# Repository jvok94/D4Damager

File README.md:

# D4 Damager
The D4 Damager is a fully-featured broadcast audio processor for AM or FM broadcasting. It can also be used as a ham radio voice processor. The D4 Damager combines six main 
features:

* **Fast peak limiting:** Prevents loud sounds from overmodulating your transmitter.
* **Compression:** A high (variable) gain input stage allows you to optionally overdrive the limiter, turning it into a compressor. This increases your audio volume without 
overmodulating, allowing you to better overcome background noise and compete with other stations.
* **Peak clipping:** Catches brief transients that overshoot the limiter, to prevent even very brief overmodulation. The limiter ensures that any clipping will only be brief and 
so does not much affect the sound.
* **Pre-emphasis:** Required for all FM transmitters, a modified version of pre-emphasis can also be used with AM transmitters to improve clarity.
* **Variable de-emphasis:** Automatically rolls off some or all of the pre-emphasis as necessary to prevent overmodulation due to the high-frequency boost.
* **Low-pass filter**: Rolls off any high frequency content that exceeds the transmitter's allowed bandwidth.

Full technical documentation will be added as soon as I get round to it.

## D4 Damager Main Board

This board implements a complete mono audio processor. For mono operation, two input connectors (J5 and J6) are provided to sum stereo sources to mono. Two boards can be linked 
together for stereo operation by joining the "STEREO LINK" connector (J4) on each board.

The PCB includes a full power supply requiring only a 15-0-15VAC (30VAC center tapped) supply from an external transformer. The power supply on a single PCB is capable of 
powering a full stereo system including all accessories (simply leave the power supply components un-populated on the second PCB). +/-15VDC power is also available on the two 
"EXT PWR" connectors (J8 and J9). Alternatively these connectors can be used to power the D4 Damager from an external +/-15VDC regulated PSU, in which case there is no need to 
fit the power supply components on the main PCB.

Controls are provided for:

* **Input gain (RV6):** Used both to match the D4 Damager to the signal level from the external audio source, and also to control how hard the limiter is driven to achieve the 
desired amount of compression.
* **Release time (RV3):** Controls how quickly the compressor/limiter returns to full gain after a transient. Influences how aggressive the compressor will sound.
* **Ratio (RV1):** Sets the maximum gain of the compressor/limiter during quiet passages. Useful to prevent excessive gain from boosting background noise, hum, hiss, etc.
* **Clipper clearance (RV4):** Sets the difference (clearance) between the limiter's output level and the clipper's clipping level. Used to trade off between maximum volume and 
minimum distortion.
* **Output gain (RV5):** Used to match the output level to your transmitter. Has no affect on the sound.

In a mono system, you have the choice of using either PCB-mount potentiometers (Bourns PTD90 series), or external panel-mount potentiometers wired to the board. In a stereo 
system, you will need to use panel-mount dual gang potentiometers to control both channels at once. In this case the two series connected dual-gang 500k potentiometers (RV1 and 
RV3) can be replaced with single 1M units. Take care to use the correct potentiometer law (RV4-RV6 are antilog types, which are unusual).

## LED Meter Bridge

Optional accessory containing four separate six-segment LED meters showing:

* Input signal level/limiter drive (VU response ref. to +12VU)
* Limiter gain reduction (reads right-to-left as standard for compressors)
* Pre-emphasis reduction (reads right-to-left)
* Output signal level (VU response ref. to +6VU)

Single connection to the main PCB via "METER BRIDGE" connector (J3) carries all signals and power. Use two PCBs in a stereo system.

## Balanced IO Card

Converts unbalanced inputs and outputs from/to balanced signals for connection to professional studio equipment. Contains two balanced receivers for stereo input, and two 
balanced transmitters for stereo output. Additionally contains two MONITOR outputs which are fully de-emphasised to drive studio monitors. All balanced inputs and outputs are 
available on both XLR and 1/4" TRS connectors.

Powered from main PCB via "EXT PWR" connector (J8 or J9).

## BoM Versions

Several different BoM versions are available to account for different broadcast standards around the world:

* **BoM fm na.xlsx:** For FM broadcasters in ITU Region 2 (North/South America). 15kHz audio bandwidth, 75us pre-emphasis time constant.
* **BoM fm row.xlsx:** For FM broadcasters in ITU Regions 1 (Africa, Europe, Middle East, North Asia) and 3 (South Asia, Oceania). 15kHz audio bandwidth, 50us pre-emphasis time 
constant.
* **BoM am na.xlsx:** For AM broadcasters in ITU Region 2 (North/South America). 5kHz audio bandwdith, pre-emphasis according to NRSC-1-C curve.
* **BoM am row.xlsx:** For AM broadcasters in ITU Regions 1 (Africa, Europe, Middle East, North Asia) and 3 (South Asia, Oceania). 4.5kHz audio bandwidth, pre-emphasis 
according to modified version of NRSC-1-C curve for reduced bandwidth.

BoM variants apply to main PCB and balanced IO card. LED VU meter card is the same worldwide.

## Initial calibration

You will need:

* Multimeter or DC voltmeter
* Dual-channel oscilloscope or audio millivolt meter
* Sine wave audio signal generator (you can use an app on your phone/PC for this, e.g. https://play.google.com/store/apps/details?id=com.keuwl.functiongenerator)

### Main PCB

Calibration should be done with no signal applied.

1. Adjust RV2 (SET DC) for 0.0mV DC offset on U1 pin 7.
2. Adjust RV7 (SET DC) for 0.0mV DC offset on U6 pin 1.

### LED VU Meter

Calibration should be done with LED VU meter PCB connected to main PCB. Make sure controls on main PCB are set as follows:

* RV1, RV3 fully clockwise.
* RV4, RV5, RV6 fully counter-clockwise.

1. Adjust RV1 (on the LED VU meter PCB) for -1.736VDC at junction of R6/R7.
2. Connect signal generator to main PCB input connector (J5). Do not apply a signal yet.
3. Connect oscilloscope channel 1 probe to main PCB input connector (J6), and channel 2 probe to main PCB output connector (J1). Use the connector shells for the ground clips.
4. Set signal generator output to 100mV p-p at 1kHz.
5. By comparing the signal levels on oscilloscope channels 1/2, measure the system gain.
6. Increase the signal generator output voltage while monitoring the gain on the oscilloscope, until the system gain has fallen 18dB below the previously measured level. This 
will require some back-and-forth between the signal generator and the oscilloscope.
7. Adjust RV3 (on the LED VU meter PCB) until D17 just lights up.
8. Without changing any signal levels, measure the DC voltage at U3 pin 6 on the main PCB.
9. Adjust the signal generator output level until the DC voltage at U3 pin 2 on the main PCB matches the voltage measured in step 8.
10. Adjust RV2 (on the LED VU meter PCB) until D23 just lights up.

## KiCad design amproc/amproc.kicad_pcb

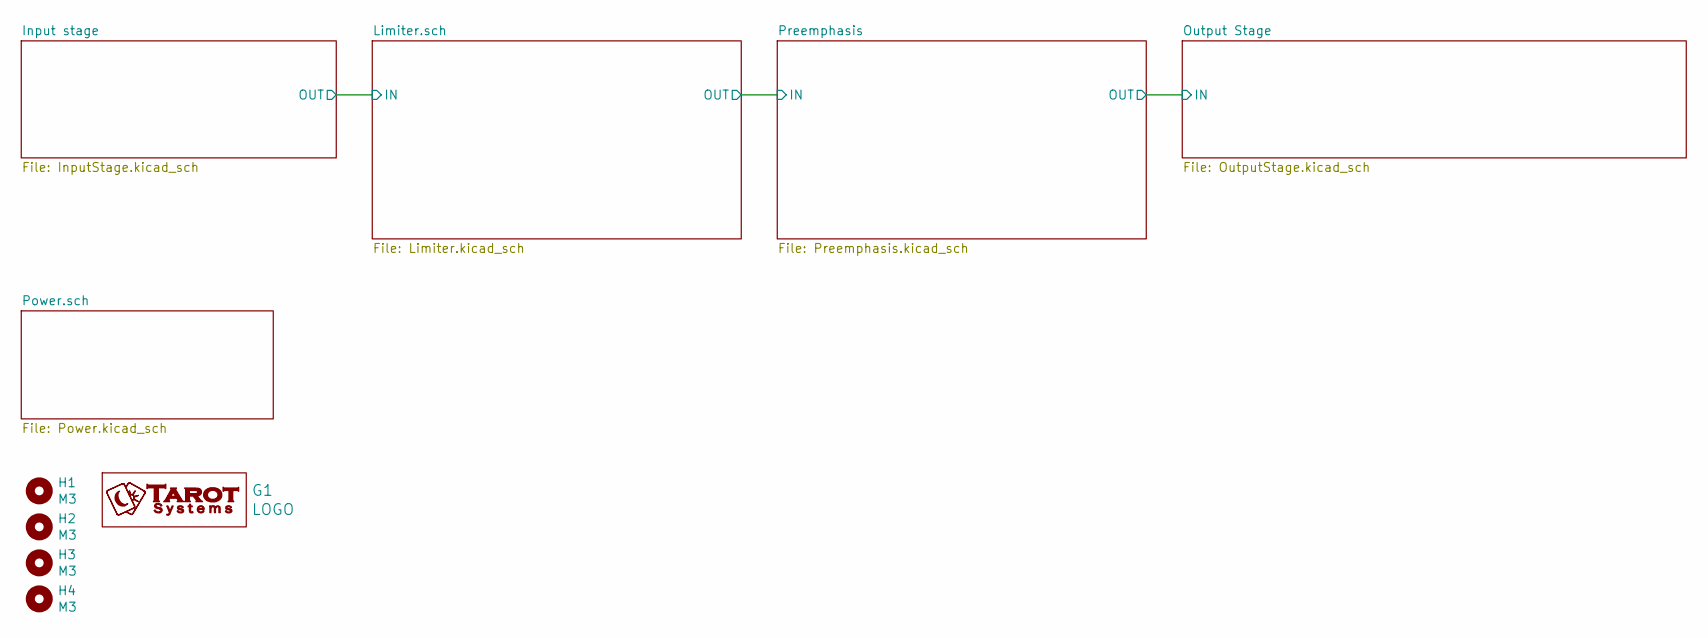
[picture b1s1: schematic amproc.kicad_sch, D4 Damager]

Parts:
G1: LOGO; tarot_logo_fsilk_25mm
H1, H2, H3, H4: M3; MountingHole_3.2mm_M3

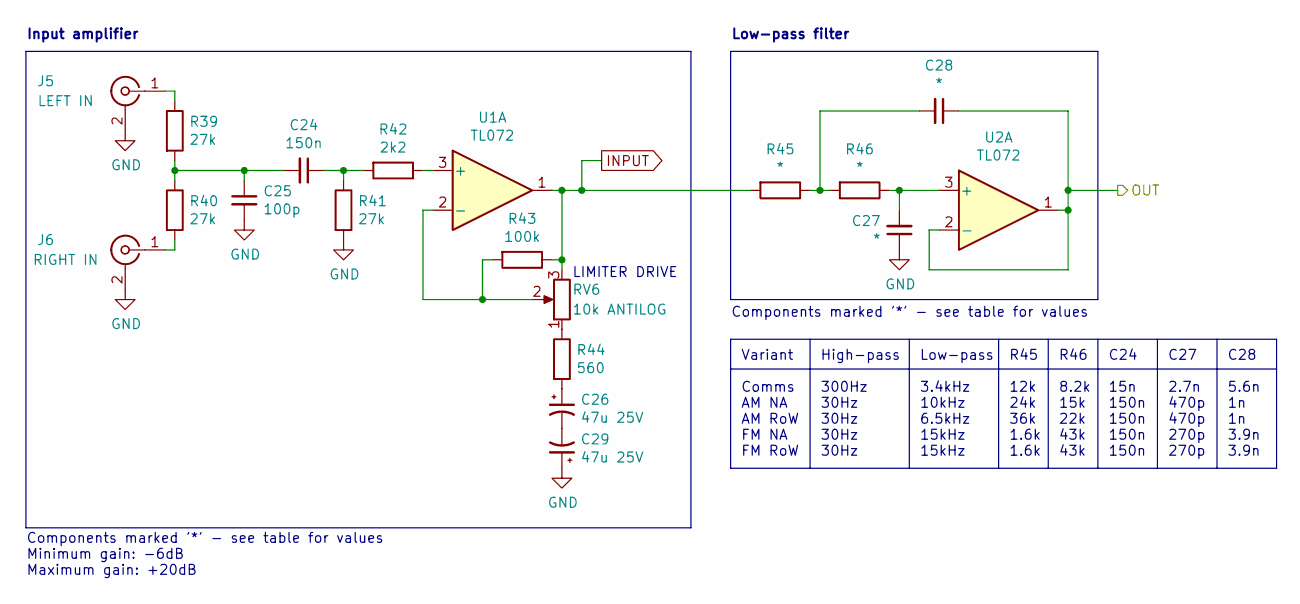
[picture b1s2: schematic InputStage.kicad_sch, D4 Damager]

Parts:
C24: 150n; C_Rect_L7.2mm_W2.5mm_P5.00mm_FKS2_FKP2_MKS2_MKP2
C25: 100p; C_Disc_D5.0mm_W2.5mm_P2.50mm
C26, C29: 47u 25V; CP_Radial_D5.0mm_P2.00mm
C27, C28: *; C_Rect_L7.2mm_W2.5mm_P5.00mm_FKS2_FKP2_MKS2_MKP2
J5: LEFT IN; NYS354
J6: RIGHT IN; NYS354
R39, R40, R41: 27k; R_Axial_DIN0207_L6.3mm_D2.5mm_P7.62mm_Horizontal_FabText
R42: 2k2; R_Axial_DIN0207_L6.3mm_D2.5mm_P7.62mm_Horizontal_FabText
R43: 100k; R_Axial_DIN0207_L6.3mm_D2.5mm_P7.62mm_Horizontal_FabText
R44: 560; R_Axial_DIN0207_L6.3mm_D2.5mm_P7.62mm_Horizontal_FabText
R45, R46: *; R_Axial_DIN0207_L6.3mm_D2.5mm_P7.62mm_Horizontal_FabText
RV6: 10k ANTILOG; PTD901-15K
U1, U2: TL072; DIP-8_W7.62mm_LongPads

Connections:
/Input stage/OUT: C28.1, U2.1, U2.2 (-); also elsewhere on the board
GND: C25.2, C27.1, C29.1, J5.2 (Ext), J6.2 (Ext), R41.2; also elsewhere on the board
INPUT: R43.1, R45.2, RV6.3, U1.1; also elsewhere on the board
unnamed: C24.1, R41.1, R42.2
unnamed: C24.2, C25.1, R39.2, R40.1
unnamed: C26.1, R44.2
unnamed: C26.2, C29.2
unnamed: C27.2, R46.1, U2.3 (+)
unnamed: C28.2, R45.1, R46.2
unnamed: J5.1 (In), R39.1
unnamed: J6.1 (In), R40.2
unnamed: R42.1, U1.3 (+)
unnamed: R43.2, RV6.2, U1.2 (-)
unnamed: R44.1, RV6.1

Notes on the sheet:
C24 15n 150n 150n 150n 150n
LIMITER DRIVE
C28 5.6n 1n 1n 3.9n 3.9n
R46 8.2k 15k 22k 43k 43k
Variant Comms AM NA AM RoW FM NA FM RoW
Low-pass filter
C27 2.7n 470p 470p 270p 270p
Components marked '*' - see table for values Minimum gain: -6dB Maximum gain: +20dB
Low-pass 3.4kHz 10kHz 6.5kHz 15kHz 15kHz
Components marked '*' - see table for values
High-pass 300Hz 30Hz 30Hz 30Hz 30Hz
Input amplifier
R45 12k 24k 36k 1.6k 1.6k

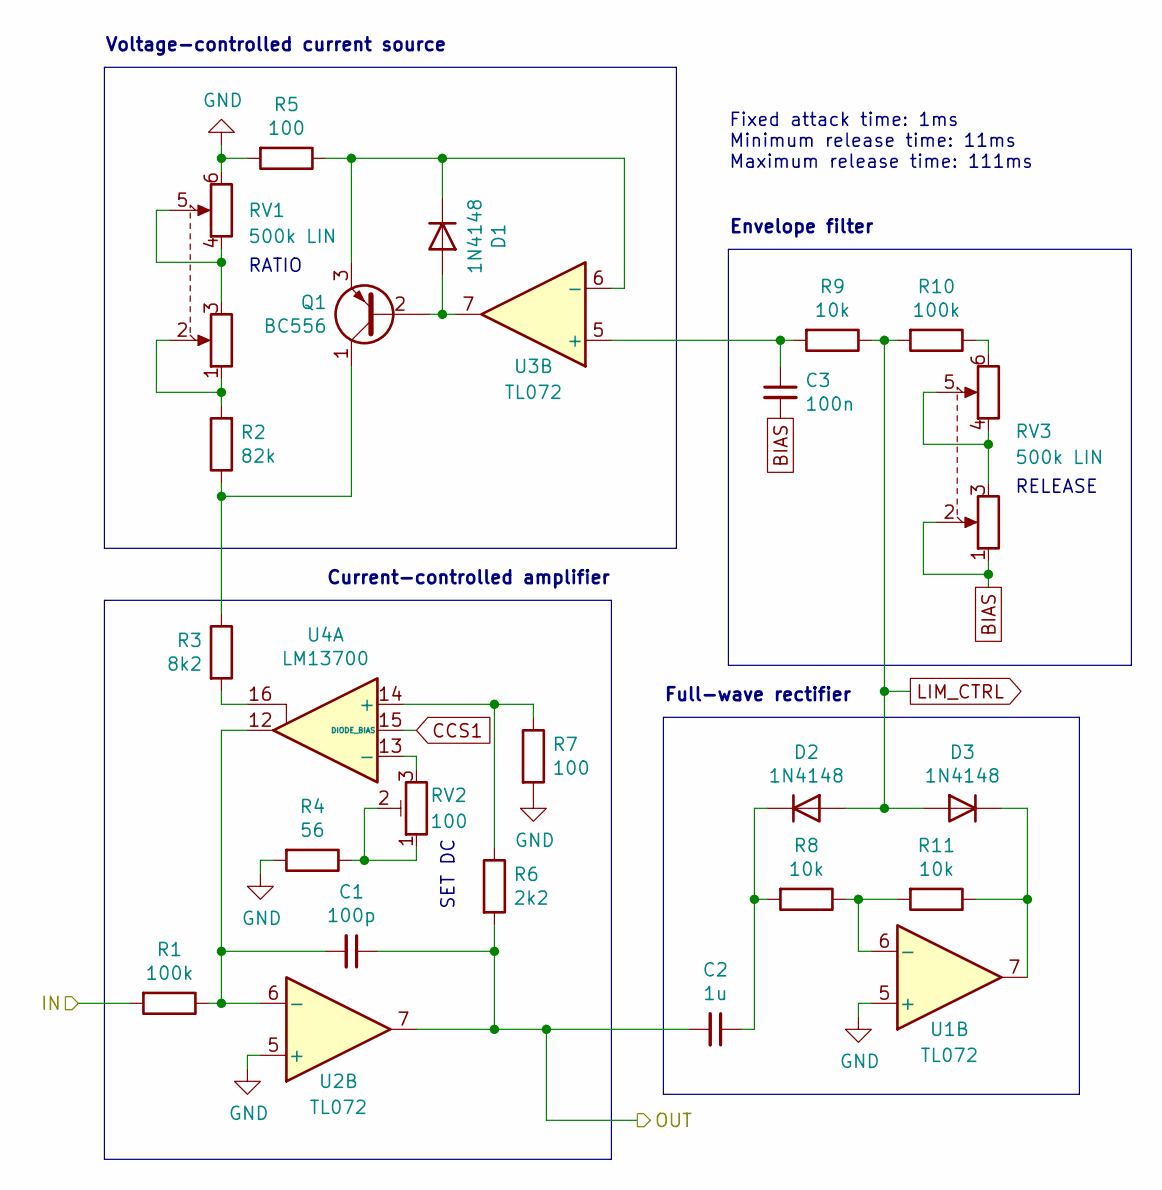
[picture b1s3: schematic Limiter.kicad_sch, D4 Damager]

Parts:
C1: 100p; C_Disc_D5.0mm_W2.5mm_P2.50mm
C2: 1u; C_Rect_L7.2mm_W5.5mm_P5.00mm_FKS2_FKP2_MKS2_MKP2
C3: 100n; C_Rect_L7.2mm_W2.5mm_P5.00mm_FKS2_FKP2_MKS2_MKP2
D1, D2, D3: 1N4148; D_DO-35_SOD27_P7.62mm_Horizontal
Q1: BC556; TO-92_Inline_Narrow_Oval
R1, R10: 100k; R_Axial_DIN0207_L6.3mm_D2.5mm_P7.62mm_Horizontal_FabText
R2: 82k; R_Axial_DIN0207_L6.3mm_D2.5mm_P7.62mm_Horizontal_FabText
R3: 8k2; R_Axial_DIN0207_L6.3mm_D2.5mm_P7.62mm_Horizontal_FabText
R4: 56; R_Axial_DIN0207_L6.3mm_D2.5mm_P7.62mm_Horizontal_FabText
R5, R7: 100; R_Axial_DIN0207_L6.3mm_D2.5mm_P7.62mm_Horizontal_FabText
R6: 2k2; R_Axial_DIN0207_L6.3mm_D2.5mm_P7.62mm_Horizontal_FabText
R8, R9, R11: 10k; R_Axial_DIN0207_L6.3mm_D2.5mm_P7.62mm_Horizontal_FabText
RV1, RV3: 500k LIN; PTD902-15K
RV2: 100; Potentiometer_Trimmer_Bourns_3296W_FabText
U1, U2, U3: TL072; DIP-8_W7.62mm_LongPads
U4: LM13700; DIP-16_W7.62mm_LongPads

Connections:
/Input stage/OUT: R1.2; also elsewhere on the board
/Limiter.sch/OUT: C1.1, C2.2, R6.2, U2.7; also elsewhere on the board
BIAS: C3.2, RV3.1, RV3.2; also elsewhere on the board
CCS1: U4.15 (DIODE_BIAS); also elsewhere on the board
GND: R4.2, R5.2, R7.2, RV1.6, U1.5 (+), U2.5 (+); also elsewhere on the board
LIM_CTRL: D2.2 (A), D3.2 (A), R9.1, R10.2; also elsewhere on the board
unnamed: C1.2, R1.1, U2.6 (-), U4.12
unnamed: C2.1, D2.1 (K), R8.2
unnamed: C3.1, R9.2, U3.5 (+)
unnamed: D1.1 (K), Q1.3 (E), R5.1, U3.6 (-)
unnamed: D1.2 (A), Q1.2 (B), U3.7
unnamed: D3.1 (K), R11.1, U1.7
unnamed: Q1.1 (C), R2.1, R3.1
unnamed: R2.2, RV1.1, RV1.2
unnamed: R3.2, U4.16
unnamed: R4.1, RV2.1, RV2.2
unnamed: R6.1, R7.1, U4.14 (+)
unnamed: R10.1, RV3.6
unnamed: R8.1, R11.2, U1.6 (-)
unnamed: RV1.3, RV1.4, RV1.5
unnamed: RV2.3, U4.13 (-)
unnamed: RV3.3, RV3.4, RV3.5

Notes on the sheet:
RATIO
SET DC
RELEASE
Fixed attack time: 1ms Minimum release time: 11ms Maximum release time: 111ms
Full-wave rectifier
Voltage-controlled current source
Envelope filter
Current-controlled amplifier

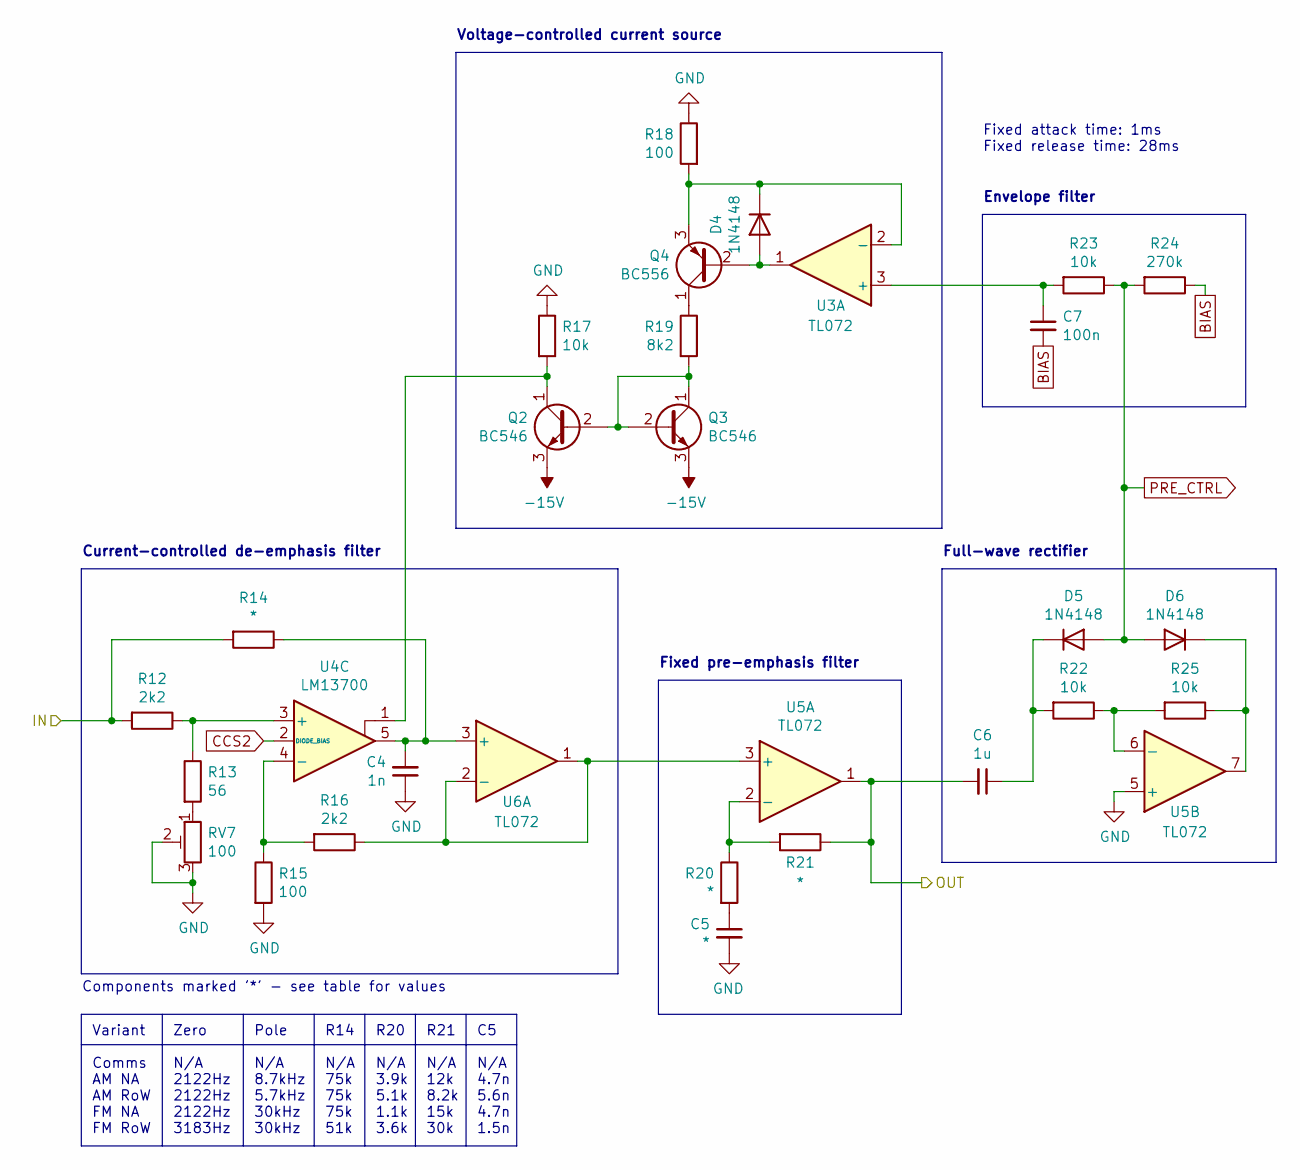
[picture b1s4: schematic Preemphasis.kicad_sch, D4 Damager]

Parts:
C4: 1n; C_Rect_L7.2mm_W2.5mm_P5.00mm_FKS2_FKP2_MKS2_MKP2
C5: *; C_Rect_L7.2mm_W2.5mm_P5.00mm_FKS2_FKP2_MKS2_MKP2
C6: 1u; C_Rect_L7.2mm_W5.5mm_P5.00mm_FKS2_FKP2_MKS2_MKP2
C7: 100n; C_Rect_L7.2mm_W2.5mm_P5.00mm_FKS2_FKP2_MKS2_MKP2
D4, D5, D6: 1N4148; D_DO-35_SOD27_P7.62mm_Horizontal
Q2, Q3: BC546; TO-92_Inline_Narrow_Oval
Q4: BC556; TO-92_Inline_Narrow_Oval
R12, R16: 2k2; R_Axial_DIN0207_L6.3mm_D2.5mm_P7.62mm_Horizontal_FabText
R13: 56; R_Axial_DIN0207_L6.3mm_D2.5mm_P7.62mm_Horizontal_FabText
R14, R20, R21: *; R_Axial_DIN0207_L6.3mm_D2.5mm_P7.62mm_Horizontal_FabText
R15, R18: 100; R_Axial_DIN0207_L6.3mm_D2.5mm_P7.62mm_Horizontal_FabText
R17, R22, R23, R25: 10k; R_Axial_DIN0207_L6.3mm_D2.5mm_P7.62mm_Horizontal_FabText
R19: 8k2; R_Axial_DIN0207_L6.3mm_D2.5mm_P7.62mm_Horizontal_FabText
R24: 270k; R_Axial_DIN0207_L6.3mm_D2.5mm_P7.62mm_Horizontal_FabText
RV7: 100; Potentiometer_Trimmer_Bourns_3296W_FabText
U3, U5, U6: TL072; DIP-8_W7.62mm_LongPads
U4: LM13700; DIP-16_W7.62mm_LongPads

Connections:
-15V: Q2.3 (E), Q3.3 (E); also elsewhere on the board
/Limiter.sch/OUT: R12.2, R14.2; also elsewhere on the board
/Output Stage/IN: C6.2, R21.1, U5.1; also elsewhere on the board
BIAS: C7.2, R24.1; also elsewhere on the board
CCS2: U4.2 (DIODE_BIAS); also elsewhere on the board
GND: C4.1, C5.2, R15.2, R17.1, R18.1, RV7.2, RV7.3, U5.5 (+); also elsewhere on the board
unnamed: C4.2, R14.1, U4.5, U6.3 (+)
unnamed: C5.1, R20.2
unnamed: C6.1, D5.1 (K), R22.2
unnamed: C7.1, R23.2, U3.3 (+)
unnamed: D4.1 (K), Q4.3 (E), R18.2, U3.2 (-)
unnamed: D4.2 (A), Q4.2 (B), U3.1
unnamed: D6.1 (K), R25.1, U5.7
unnamed: Q2.1 (C), R17.2, U4.1
unnamed: Q2.2 (B), Q3.1 (C), Q3.2 (B), R19.2
unnamed: Q4.1 (C), R19.1
unnamed: R12.1, R13.1, U4.3 (+)
unnamed: R13.2, RV7.1
unnamed: R15.1, R16.2, U4.4 (-)
unnamed: R16.1, U5.3 (+), U6.1, U6.2 (-)
unnamed: R20.1, R21.2, U5.2 (-)
unnamed: R22.1, R25.2, U5.6 (-)
PRE_CTRL: D5.2 (A), D6.2 (A), R23.1, R24.2; also elsewhere on the board

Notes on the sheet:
R21 N/A 12k 8.2k 15k 30k
Voltage-controlled current source
Fixed pre-emphasis filter
Fixed attack time: 1ms Fixed release time: 28ms
R14 N/A 75k 75k 75k 51k
Components marked '*' - see table for values
Variant Comms AM NA AM RoW FM NA FM RoW
Current-controlled de-emphasis filter
C5 N/A 4.7n 5.6n 4.7n 1.5n
Envelope filter
Full-wave rectifier
Pole N/A 8.7kHz 5.7kHz 30kHz 30kHz
Zero N/A 2122Hz 2122Hz 2122Hz 3183Hz
R20 N/A 3.9k 5.1k 1.1k 3.6k

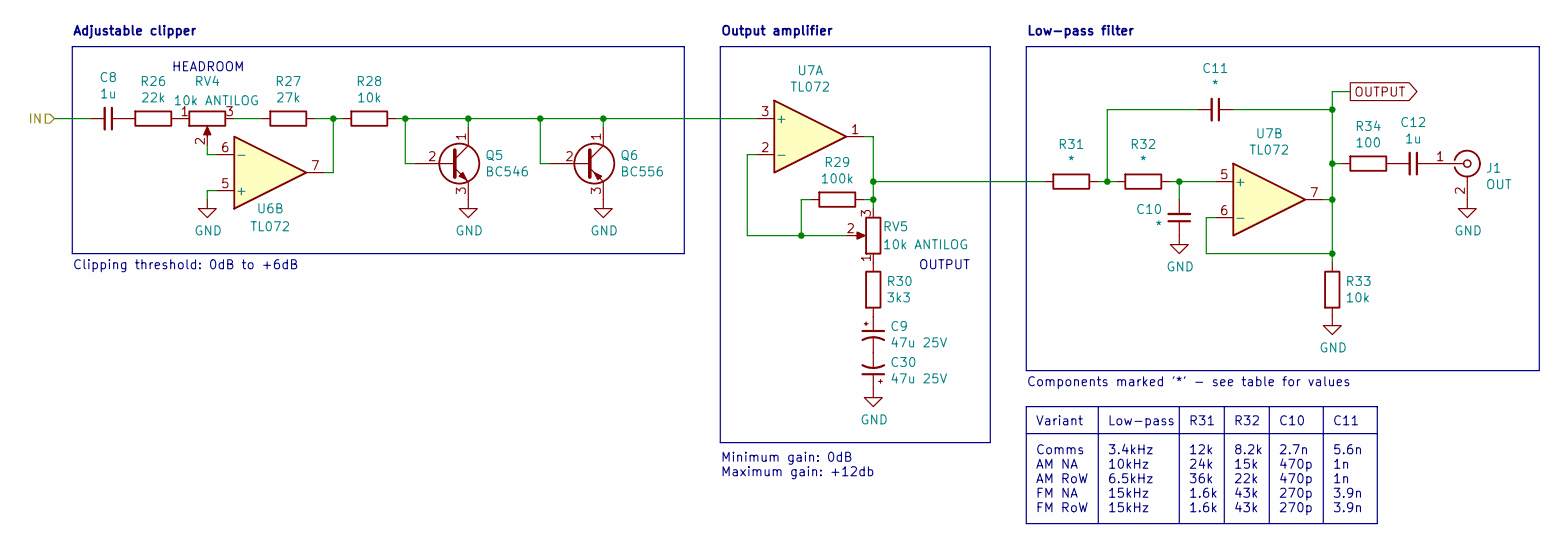
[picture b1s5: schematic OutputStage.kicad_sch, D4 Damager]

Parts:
C8, C12: 1u; C_Rect_L7.2mm_W5.5mm_P5.00mm_FKS2_FKP2_MKS2_MKP2
C9, C30: 47u 25V; CP_Radial_D5.0mm_P2.00mm
C10, C11: *; C_Rect_L7.2mm_W2.5mm_P5.00mm_FKS2_FKP2_MKS2_MKP2
J1: OUT; NYS354
Q5: BC546; TO-92_Inline_Narrow_Oval
Q6: BC556; TO-92_Inline_Narrow_Oval
R26: 22k; R_Axial_DIN0207_L6.3mm_D2.5mm_P7.62mm_Horizontal_FabText
R27: 27k; R_Axial_DIN0207_L6.3mm_D2.5mm_P7.62mm_Horizontal_FabText
R28, R33: 10k; R_Axial_DIN0207_L6.3mm_D2.5mm_P7.62mm_Horizontal_FabText
R29: 100k; R_Axial_DIN0207_L6.3mm_D2.5mm_P7.62mm_Horizontal_FabText
R30: 3k3; R_Axial_DIN0207_L6.3mm_D2.5mm_P7.62mm_Horizontal_FabText
R31, R32: *; R_Axial_DIN0207_L6.3mm_D2.5mm_P7.62mm_Horizontal_FabText
R34: 100; R_Axial_DIN0207_L6.3mm_D2.5mm_P7.62mm_Horizontal_FabText
RV4, RV5: 10k ANTILOG; PTD901-15K
U6, U7: TL072; DIP-8_W7.62mm_LongPads

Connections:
/Output Stage/IN: C8.2; also elsewhere on the board
GND: C10.1, C30.1, J1.2 (Ext), Q5.3 (E), Q6.3 (E), R33.2, U6.5 (+); also elsewhere on the board
unnamed: C8.1, R26.2
unnamed: C9.1, R30.2
unnamed: C10.2, R32.1, U7.5 (+)
unnamed: C11.2, R31.1, R32.2
unnamed: C12.1, J1.1 (In)
unnamed: C12.2, R34.1
unnamed: C9.2, C30.2
unnamed: Q5.1 (C), Q5.2 (B), Q6.1 (C), Q6.2 (B), R28.1, U7.3 (+)
unnamed: R26.1, RV4.1
unnamed: R27.1, R28.2, U6.7
unnamed: R27.2, RV4.3
unnamed: R29.1, R31.2, RV5.3, U7.1
unnamed: R29.2, RV5.2, U7.2 (-)
unnamed: R30.1, RV5.1
unnamed: RV4.2, U6.6 (-)
OUTPUT: C11.1, R33.1, R34.2, U7.6 (-), U7.7; also elsewhere on the board

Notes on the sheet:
HEADROOM
Adjustable clipper
Output amplifier
Minimum gain: 0dB Maximum gain: +12db
OUTPUT
R32 8.2k 15k 22k 43k 43k
Clipping threshold: 0dB to +6dB
R31 12k 24k 36k 1.6k 1.6k
Components marked '*' - see table for values
Low-pass 3.4kHz 10kHz 6.5kHz 15kHz 15kHz
C10 2.7n 470p 470p 270p 270p
Low-pass filter
Variant Comms AM NA AM RoW FM NA FM RoW
C11 5.6n 1n 1n 3.9n 3.9n

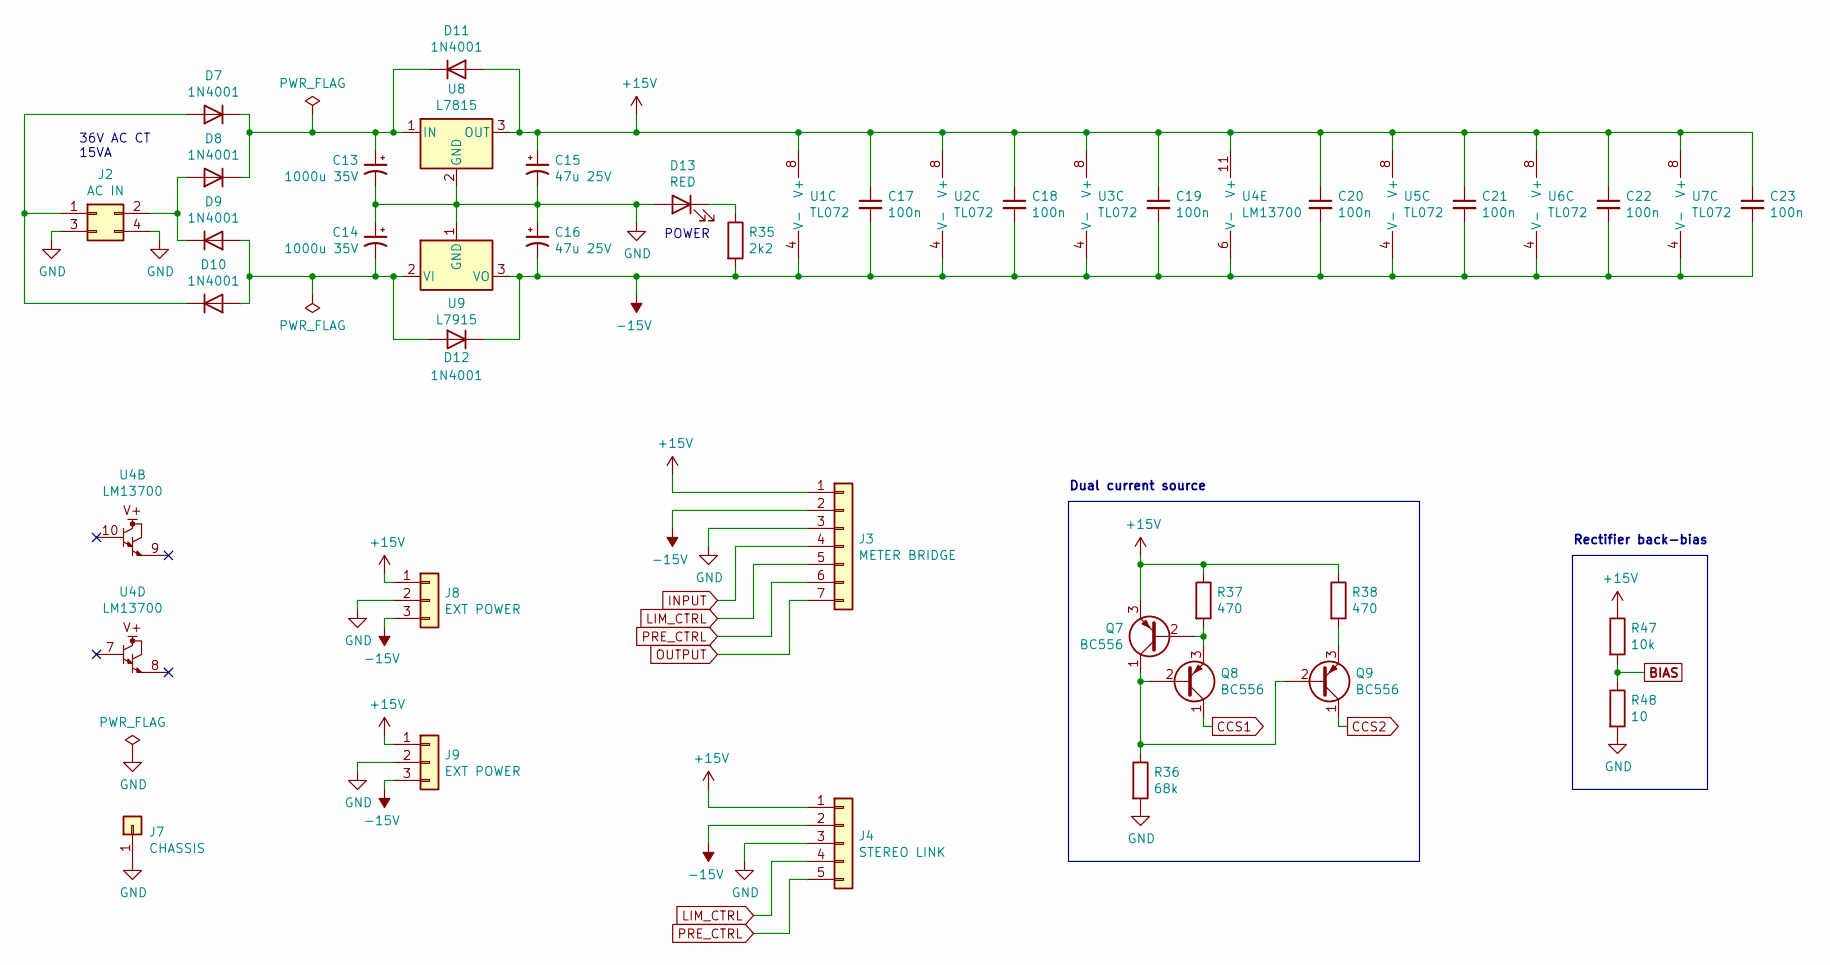
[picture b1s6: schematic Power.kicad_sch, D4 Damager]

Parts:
C13, C14: 1000u 35V; CP_Radial_D12.5mm_P5.00mm
C15, C16: 47u 25V; CP_Radial_D5.0mm_P2.00mm
C17, C18, C19, C20, C21, C22, C23: 100n; C_Disc_D4.7mm_W2.5mm_P5.00mm
D7, D8, D9, D10, D11, D12: 1N4001; D_DO-41_SOD81_P10.16mm_Horizontal
D13: RED; LED_D5.0mm
J2: AC IN; 39-28-1043
J3: METER BRIDGE; JST_XH_B07B-XH-A_07x2.50mm_Straight
J4: STEREO LINK; JST_XH_B05B-XH-A_05x2.50mm_Straight
J7: CHASSIS; TAB_378005.68
J8, J9: EXT POWER; JST_XH_B03B-XH-A_03x2.50mm_Straight
Q7, Q8, Q9: BC556; TO-92_Inline_Narrow_Oval
R35: 2k2; R_Axial_DIN0207_L6.3mm_D2.5mm_P7.62mm_Horizontal_FabText
R36: 68k; R_Axial_DIN0207_L6.3mm_D2.5mm_P7.62mm_Horizontal_FabText
R37, R38: 470; R_Axial_DIN0207_L6.3mm_D2.5mm_P7.62mm_Horizontal_FabText
R47: 10k; R_Axial_DIN0207_L6.3mm_D2.5mm_P7.62mm_Horizontal_FabText
R48: 10; R_Axial_DIN0207_L6.3mm_D2.5mm_P7.62mm_Horizontal_FabText
U1, U2, U3, U5, U6, U7: TL072; DIP-8_W7.62mm_LongPads
U4: LM13700; DIP-16_W7.62mm_LongPads
U8: L7815; TO-220-3_Horizontal_TabUp
U9: L7915; TO-220-3_Horizontal_TabUp

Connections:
+15V: C15.1, C17.1, C18.1, C19.1, C20.1, C21.1, C22.1, C23.1, D11.2 (A), J3.1, J4.1, J8.1, J9.1, Q7.3 (E), R37.1, R38.1, R47.1, U1.8 (V+), U2.8 (V+), U3.8 (V+), U4.11 (V+), U5.8 (V+), U6.8 (V+), U7.8 (V+), U8.3 (OUT)
-15V: C16.2, C17.2, C18.2, C19.2, C20.2, C21.2, C22.2, C23.2, D12.1 (K), J3.2, J4.2, J8.3, J9.3, R35.2, U1.4 (V-), U2.4 (V-), U3.4 (V-), U4.6 (V-), U5.4 (V-), U6.4 (V-), U7.4 (V-), U9.3 (VO); also elsewhere on the board
BIAS: R47.2, R48.1; also elsewhere on the board
CCS1: Q8.1 (C); also elsewhere on the board
CCS2: Q9.1 (C); also elsewhere on the board
GND: C13.2, C14.1, C15.2, C16.1, D13.2 (A), J2.3, J2.4, J3.3, J4.3, J7.1, J8.2, J9.2, R36.2, R48.2, U8.2 (GND), U9.1 (GND); also elsewhere on the board
INPUT: J3.4; also elsewhere on the board
LIM_CTRL: J3.5, J4.4; also elsewhere on the board
unnamed: C13.1, D7.1 (K), D8.1 (K), D11.1 (K), U8.1 (IN)
unnamed: C14.2, D9.2 (A), D10.2 (A), D12.2 (A), U9.2 (VI)
unnamed: D8.2 (A), D9.1 (K), J2.2
unnamed: D7.2 (A), D10.1 (K), J2.1
unnamed: D13.1 (K), R35.1
unnamed: Q7.1 (C), Q8.2 (B), Q9.2 (B), R36.1
unnamed: Q7.2 (B), Q8.3 (E), R37.2
unnamed: Q9.3 (E), R38.2
OUTPUT: J3.7; also elsewhere on the board
PRE_CTRL: J3.6, J4.5; also elsewhere on the board

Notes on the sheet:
Dual current source
Rectifier back-bias
POWER
36V AC CT 15VA

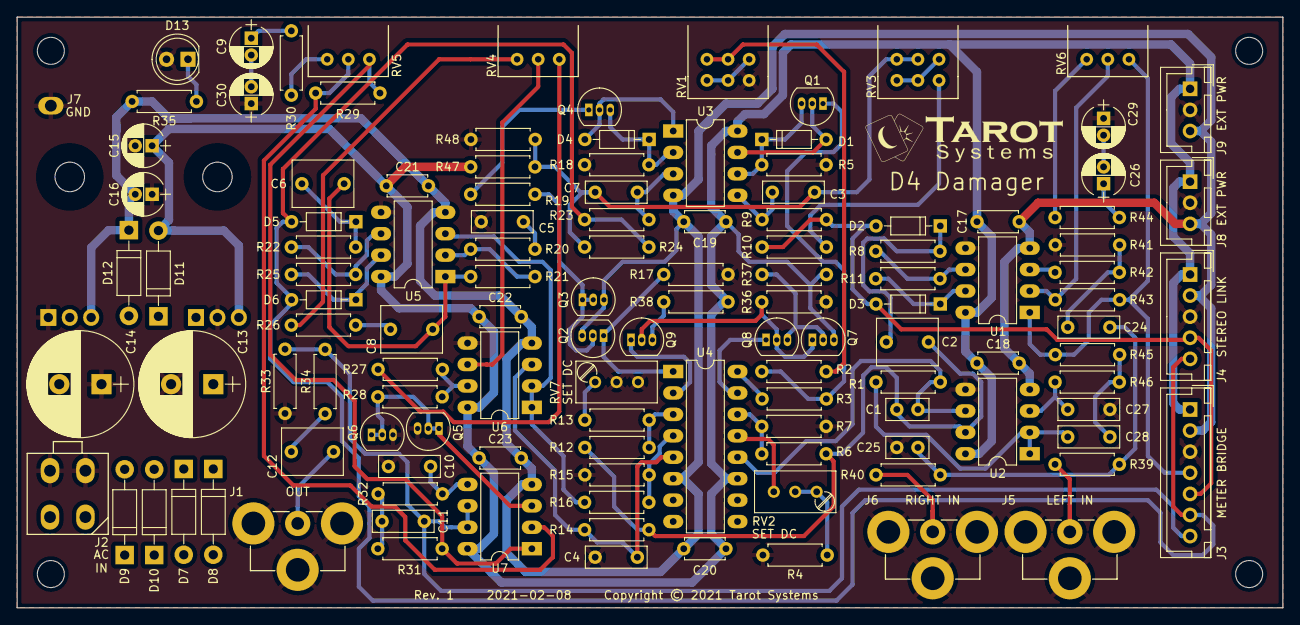
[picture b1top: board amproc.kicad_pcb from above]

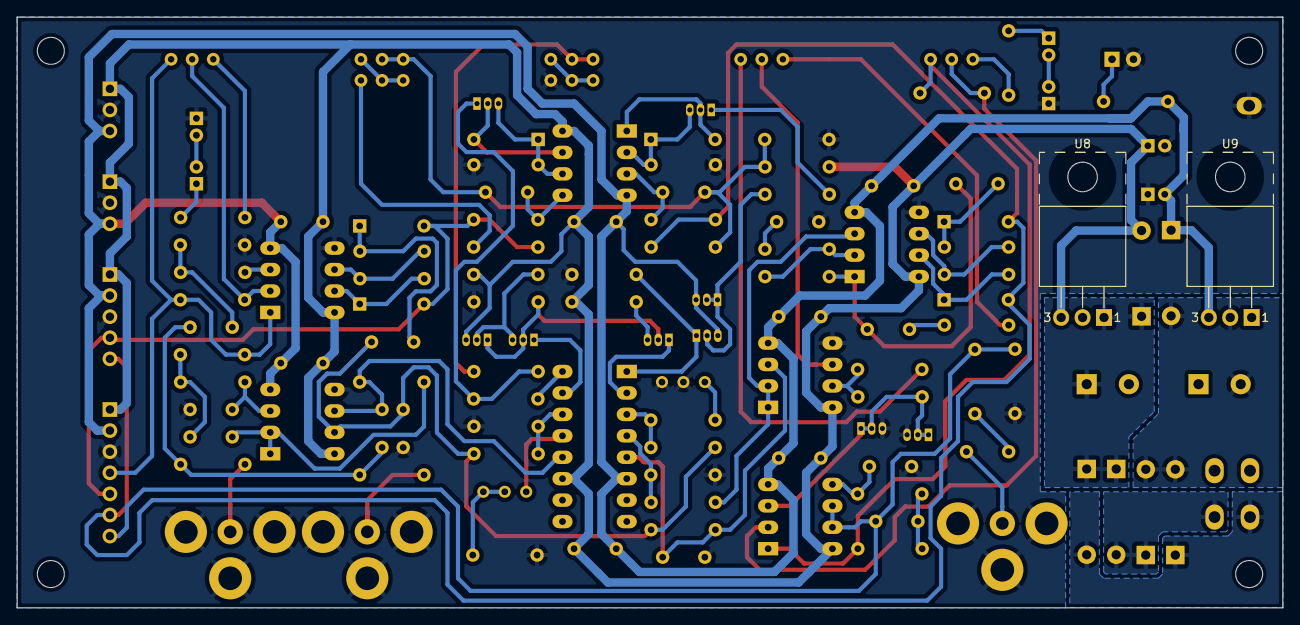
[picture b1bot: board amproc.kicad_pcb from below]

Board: 2 copper layers, 150.0 x 70.0 mm, 130 parts (2 on the bottom side), 79 nets.

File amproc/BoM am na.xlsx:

Reference | Quantity | Value | Footprint | Description | Manufacturer | Part number | Supplier | Order code | Price | Total | Notes
C1 C25 | 2 | 100p | Radial disc W4mm T2.6mm S2.5mm | 100pF 50V 5% C0G | Vishay | K101J15C0GF5TL2 | Farnell | 2860078 | 7.1300000000000002E-2 | 0.1426
C10 C27 | 2 | 470p | Radial disc W4mm T2.5mm S5mm | 470pF 60V 5% C0G | Murata | RDE5C1H471J0M1H03A | Farnell | 2990775 | 0.16 | 0.32
C14 C13 | 2 | 1000u 35V | Radial can D12mm S5mm | 1000uF 35V 20% 105C electrolytic | Kemet | ESY108M035AL4AA | Farnell | 2835188 | 0.439 | 0.878
C17 C18 C19 C21 C20 C22 C23 | 7 | 100n | Radial disc W4mm T2.6mm S5mm | 100nF 50V 10% X7R | Vishay | K104K15X7RF53H5 | Farnell | 1141777 | 8.2299999999999998E-2 | 0.57609999999999995
C3 C7 | 2 | 100n | Radial box W7.2mm T2.5mm S5mm | 100nF 63V 10% film | Kemet | R82DC3100AA50K | Farnell | 2763208 | 0.128 | 0.25600000000000001
C24 | 1 | 150n | Radial box W7.2mm T2.5mm S5mm | 150nF 63V 10% film | Kemet | R82DC3150DQ60K | Farnell | 2446334 | 0.13700000000000001 | 0.13700000000000001
C26 C29 C16 C15 C9 C30 | 6 | 47u 25V | Radial can D5mm S2mm | 47uF 25V 20% 105C electrolytic | Kemet | ESH476M025AC3AA | Farnell | 2068762 | 7.4499999999999997E-2 | 0.44699999999999995
C4 C11 C28 | 3 | 1n | Radial box W7.2mm T2.5mm S5mm | 1nF 100V 5% film | Kemet | R82EC1100Z350J | Farnell | 1679411 | 0.13 | 0.39
C5 | 1 | 4n7 | Radial box W7.2mm T2.5mm S5mm | 4.7nF 100V 10% film | Kemet | R82EC1470DQ50K | Farnell | 2763226 | 0.11 | 0.11
C8 C12 C6 C2 | 4 | 1u | Radial box W7.2mm T5mm 5mm | 1uF 63V 10% film | Kemet | R82DC4100AA60K | Farnell | 2763215 | 0.27500000000000002 | 1.1000000000000001
D13 | 1 | RED | T1-3/4 | 5mm 10mA red LED | Multicomp | MCL053PD | Farnell | 1581136 | 6.0900000000000003E-2 | 6.0900000000000003E-2
D4 D5 D6 D1 D2 D3 | 6 | 1N4148 | DO-35/DO-204AH | 100V 150mA silicon signal diode | Multicomp | 1N4148 (DO-35) | Farnell | 2675146 | 3.1899999999999998E-2 | 0.19139999999999999
D7 D8 D9 D10 D12 D11 | 6 | 1N4001 | DO-204AL | 50V 1A silicon power diode | ON Semiconductor | 1N4001RLG | Farnell | 2822512 | 0.193 | 1.1579999999999999
J1 J5 J6 | 3 |  | NYS354 | NYS354 | Rean | NYS354 | Mouser | 568-NYS354 | 0.59 | 1.77
J2 | 1 | AC IN | 39-28-1043 | 2x2-pin 4.20mm pitch shrouded header | Molex | 39-28-1043 | Farnell | 9732098 | 0.58099999999999996 | 0.58099999999999996 | Mates with Molex 39-01-2040 housing
J3 | 1 | METER BRIDGE | B7B-XH-A | 1x7-pin 2.5mm pitch shrouded header | JST | B7B-XH-A (LF)(SN) | Farnell | 1516283 | 0.247 | 0.247 | Mates with JST XHP-7
J4 | 1 | STEREO LINK | B5B-XH-A | 1x5-pin 2.5mm pitch shrouded header | JST | B5B-XH-A (LF)(SN) | Farnell | 1516281 | 0.13200000000000001 | 0.13200000000000001 | Mates with JST XHP-5
J7 | 1 | CHASSIS | TAB37800568 | 2.8x0.51mm PCB terminal | JST | TAB 37800568(MSTIN) | Farnell | 3625552 | 2.52E-2 | 2.52E-2 | Mates with any 2.8x0.51mm crimp terminal
J8 J9 | 2 | EXT POWER | B3B-XH-A | 1x3-pin 2.5mm pitch shrouded header | JST | B3B-XH-A (LF)(SN) | Farnell | 1516277 | 9.2499999999999999E-2 | 0.185
Q5 Q3 Q2 | 3 | BC546 | TO-92 | 100mA 65V NPN BJT | ON Semiconductor | BC546BTF | Farnell | 2453787 | 0.151 | 0.45299999999999996
Q8 Q7 Q9 Q6 Q4 Q1 | 6 | BC556 | TO-92 | 100mA 65V PNP BJT | ON Semiconductor | BC556BTF | Farnell | 2453802 | 0.16400000000000001 | 0.98399999999999999
R13 R4 | 2 | 56 | Axial 6.8mm | 56R 0.6W 1% metal film | Multicomp | MCMF006FF560JA50 | Farnell | 2401720 | 2.8799999999999999E-2 | 5.7599999999999998E-2
R14 | 1 | 75k | Axial 6.8mm | 75k 0.6W 1% metal film | Multicomp | MCMF006FF7502A50 | Farnell | 2401804 | 2.8799999999999999E-2 | 2.8799999999999999E-2
R19 R3 | 2 | 8k2 | Axial 6.8mm | 8.2k 0.6W 1% metal film | Multicomp | MCMF006FF8201A50 | Farnell | 2401778 | 2.8400000000000002E-2 | 5.6800000000000003E-2
R2 | 1 | 82k | Axial 6.8mm | 82k 0.6W 1% metal film | Multicomp | MCMF006FF8202A50 | Farnell | 2401805 | 0.03 | 0.03
R20 | 1 | 3k9 | Axial 6.8mm | 3.9k 0.6W 1% metal film | Multicomp | MCMF006FF3901A50 | Farnell | 2401768 | 3.0200000000000001E-2 | 3.0200000000000001E-2
R21 | 1 | 12k | Axial 6.8mm | 12k 0.6W 1% metal film | Multicomp | MCMF006FF1202A50 | Farnell | 2401783 | 2.8400000000000002E-2 | 2.8400000000000002E-2
R24 | 1 | 270k | Axial 6.8mm | 270k 0.6W 1% metal film | Multicomp | MCMF006FF2703A50 | Farnell | 2401818 | 2.86E-2 | 2.86E-2
R26 | 1 | 22k | Axial 6.8mm | 22k 0.6W 1% metal film | Multicomp | MCMF006FF2202A50 | Farnell | 2401789 | 0.03 | 0.03
R30 | 1 | 3k3 | Axial 6.8mm | 3.3k 0.6W 1% metal film | Multicomp | MCMF006FF3301A50 | Farnell | 2401766 | 2.8799999999999999E-2 | 2.8799999999999999E-2
R31 R45 | 2 | 24k | Axial 6.8mm | 24k 0.6W 1% metal film | Multicomp | MCMF006FF2402A50 | Farnell | 2401790 | 3.7900000000000003E-2 | 7.5800000000000006E-2
R32 R46 | 2 | 15k | Axial 6.8mm | 15k 0.6W 1% metal film | Multicomp | MCMF006FF1502A50 | Farnell | 2401785 | 3.7900000000000003E-2 | 7.5800000000000006E-2
R34 R15 R18 R7 R5 | 5 | 100 | Axial 6.8mm | 100R 0.6W 1% metal film | Multicomp | MCMF006FF1000A50 | Farnell | 2401727 | 0.03 | 0.15
R36 | 1 | 68k | Axial 6.8mm | 68k 0.6W 1% metal film | Multicomp | MCMF006FF6802A50 | Farnell | 2401803 | 2.8799999999999999E-2 | 2.8799999999999999E-2
R37 R38 | 2 | 470 | Axial 6.8mm | 470R 0.6W 1% metal film | TE Connectivity | LR1F470R | Farnell | 2330156 | 7.8600000000000003E-2 | 0.15720000000000001
R39 R40 R41 R27 | 4 | 27k | Axial 6.8mm | 27k 0.6W 1% metal film | Multicomp | MCMF006FF2702A50 | Farnell | 2401791 | 2.8400000000000002E-2 | 0.11360000000000001
R42 R35 R16 R12 R6 | 5 | 2k2 | Axial 6.8mm | 2.2k 0.6W 1% metal film | Multicomp | MCMF006FF2201A50 | Farnell | 2401762 | 2.8299999999999999E-2 | 0.14149999999999999
R43 R29 R10 R1 | 4 | 100k | Axial 6.8mm | 100k 0.6W 1% metal film | Multicomp | MCMF006FF1003A50 | Farnell | 2401807 | 2.8400000000000002E-2 | 0.11360000000000001
R44 | 1 | 560 | Axial 6.8mm | 560R 0.6W 1% metal film | Multicomp | MCMF006FF5600A50 | Farnell | 2401747 | 2.8799999999999999E-2 | 2.8799999999999999E-2
R47 R28 R33 R23 R17 R25 R22 R9 R11 R8 | 11 | 10k | Axial 6.8mm | 10k 0.6W 1% metal film | Multicomp | MCMF006FF1002A50 | Farnell | 2401780 | 2.8799999999999999E-2 | 0.31679999999999997
R48 | 1 | 10 | Axial 6.8mm | 10R 0.6W 1% metal film | Multicomp | MCMF006FF100JA50 | Farnell | 2401700 | 2.8799999999999999E-2 | 2.8799999999999999E-2
RV1 RV3 | 2 | 500k LIN | PTD902 | 500k dual gang linear potentiometer | Bourns | PTD902-1015K-B504 | Mouser | 652-PTD9021015KB504 | 1.5 | 3
RV2 RV7 | 2 | 100 | T93YA | 100R multiturn trimmer | Vishay | T93YA101KT20 | Farnell | 1141397 | 1.4 | 2.8
RV6 RV5 RV4 | 3 | 10k ANTILOG | PTD901 | 10k single gang antilog potentiometer | Bourns | PTD901-2015F-C103 | Mouser | 652-PTD9012015FC103 | 1.25 | 3.75
U1 U2 U3 U5 U6 U7 | 6 | TL072 | DIP-8 | Dual 36V JFET input opamp | Texas Instruments | TL072ACP | Farnell | 3117783 | 0.90500000000000003 | 5.43
U4 | 1 | LM13700 | DIP-16 | Dual OTA | Texas Instruments | LM13700N/NOPB | Farnell | 3118206 | 1.84 | 1.84
U8 | 1 | L7815 | TO-220 | Positive 15V linear regulator | ON Semiconductor | MC7815ACTG | Farnell | 2382331 | 0.46 | 0.46
U9 | 1 | L7915 | TO-220 | Negative 15V linear regulator | ON Semiconductor | MC7915ACTG | Mouser | 863-MC7915ACTG | 0.40400000000000003 | 0.40400000000000003
 |  |  |  |  |  |  |  |  | Total | 29.3781

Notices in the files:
amproc/InputStage.kicad_sch:
Copyright © 2020 Tarot Systems
amproc/amproc.kicad_pcb:
Copyright © 2021 Tarot Systems
Rev. 1 2021-02-08 Copyright © 2021 Tarot Systems
balio/balio.kicad_pcb:
Rev. 1 2021-01-08 Copyright © 2021 Tarot Systems
